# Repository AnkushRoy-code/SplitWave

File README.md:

<p align="center">
  <br>
</p>

# SplitWave
My very own custom wireless ergonomic split keyboard.

Splitwave is a 44 key column-staggered split keyboard that uses Choc switches.
Is is powered by SuperMini nRF52840 micro-controller. It is created during the
[Highway](https://highway.hackclub.com/) event of [Hackclub](https://hackclub.com/). The whole process of making it is journaled [here](https://github.com/AnkushRoy-code/SplitWave/blob/main/JOURNAL.md).

One day my work keyboard stopped working and I always dreamed of having those
fancy split keyboards but I was never lucky to have one at that same period of
time. HackClub announced Highway event, and I hopped into it!! The timing
couldn't have been any more perfect!!!

## Layout
<p align="center">
  <br>
  <b>Keys Layout of SplitWave</b>
</p>

## PCBs
SplitWave has a reversible PCB(which means you can order one PCB in stack and
use that for both left and right).
The KiCAD PCB file is located [here](https://github.com/AnkushRoy-code/SplitWave/blob/main/ergogen/pcb/board.kicad_pcb).

<table>
  <tr>
    <td align="center">
      <br>
      <b>Front Of the PCB</b>
    </td>
    <td align="center">
      <br>
      <b>Back Of the PCB</b>
    </td>
    <td align="center">
      <br>
      <b>PCB in KiCAD</b>
    </td>
  </tr>
</table>

## Case
The STL files for SplitWave are present [here](https://github.com/AnkushRoy-code/SplitWave/tree/main/ergogen/output/cases).
The cases are also hosted in printables.com [here](https://www.printables.com/model/1317576-splitwave-split-keyboard-cases)

<table>
  <tr>
    <td align="center">
      <br>
      <b>Top Case</b>
    </td>
    <td align="center">
      <br>
      <b>Left & Right Cases Top View</b>
    </td>
  </tr>
  <tr>
    <td align="center">
      <br>
      <b>Left & Right Cases Bottom View</b>
    </td>
    <td align="center">
      <br>
      <b>All Of Them Together</b>
    </td>
  </tr>
</table>

## Firmware
The firmware used for SplitWave is [ZMK](https://zmk.dev) and the prebuilt firmware can be found in the actions page of [this](https://github.com/AnkushRoy-code/zmk-config-splitwave) repo that I made.

## Photos
<table>
  <tr>
    <td align="center">
      <br>
    </td>
    <td align="center">
      <br>
    </td>
  </tr>
</table>

## Credits
[Hackclub](https://hackclub.com/) for giving me such an opportunity to work on my dream keyboard.

https://christianselig.com for inspiring me make my keyboard.

All the great tutorials in Youtube by [Joe Scotto](https://www.youtube.com/@joe_scotto) [Ben Vallack](https://www.youtube.com/@BenVallack) and many many more!!

Special thanks to https://flatfootfox.com for such a comprehensive and nice
tutorial on ergogen and thanks to the creator of ergogen himself and the
mantainers, contributors for making and mantaining such an amazing tool. Also
thanks a lot to ergogen discord/community for all their help!

Also thanks to https://github.com/GEIGEIGEIST/TOTEM for their readme. I didn't
know what goes into a keyboard readme so this readme is a lot inspired by the
Totem readme.

Lastly I will like to again thank hackclub for giving me such awesome
highschool years. Had a heck lot of fun all these years and had a blast making
my last [ysws](https://ysws.hackclub.com/) project. If you are (or know someone) younger than 18 or a
highschooler who is tech enthusiast then checkout hackclub it is really cool!

## License
This repo has an MIT License that in short means you can do whatever you want
with it without facing any lawsuit.

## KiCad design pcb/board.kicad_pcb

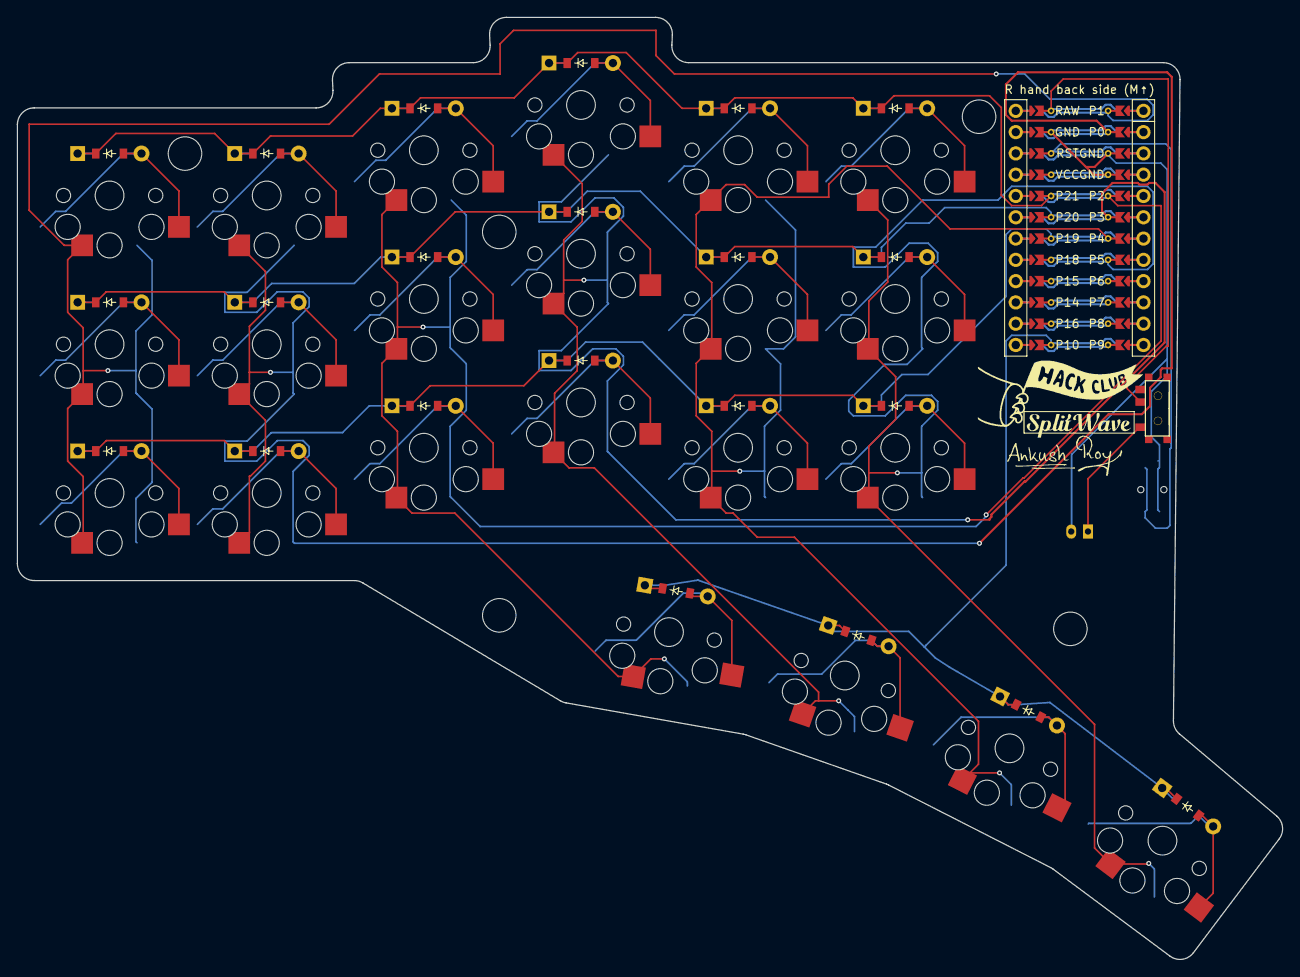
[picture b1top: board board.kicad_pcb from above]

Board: 2 copper layers, 151.0 x 112.4 mm, 48 parts (0 on the bottom side), 36 nets.

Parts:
B1: Panasonic_EVQPUL_EVQPUC
D1, D2, D3, D4, D5, D6, D7, D8, D9, D10, D11, D12, D13, D14, D15, D16, D17, D18, D19, D20, D21, D22: ComboDiode
JST1: JST_PH_S2B-PH-K_02x2.00mm_Angled
MCU1: mcu_supermini_nrf52840
S1, S2, S3, S4, S5, S6, S7, S8, S9, S10, S11, S12, S13, S14, S15, S16, S17, S18, S19, S20, S21, S22: PG1350
T1: SPDT_C128955

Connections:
GND: B1.1, JST1.2, MCU1.103, MCU1.104, MCU1.123
P0: MCU1.102, S4.1, S5.1, S6.1
P1: MCU1.101, S1.1, S2.1, S3.1
P2: MCU1.105, S7.1, S8.1, S9.1, S19.1
P3: MCU1.106, S10.1, S11.1, S12.1, S20.1
P4: MCU1.107, S13.1, S14.1, S15.1, S21.1
P5: MCU1.108, S16.1, S17.1, S18.1, S22.1
P10: D19.1, D20.1, D21.1, D22.1, MCU1.113
P19: D1.1, D4.1, D7.1, D10.1, D13.1, D16.1, MCU1.118
P20: D2.1, D5.1, D8.1, D11.1, D14.1, D17.1, MCU1.119
P21: D3.1, D6.1, D9.1, D12.1, D15.1, D18.1, MCU1.120
RAW: MCU1.124, T1.2
RST: B1.2, MCU1.122
four_cluster: D22.2, S22.2
index_bottom: D13.2, S13.2
index_home: D14.2, S14.2
index_top: D15.2, S15.2
inner_bottom: D16.2, S16.2
inner_home: D17.2, S17.2
inner_top: D18.2, S18.2
middle_bottom: D10.2, S10.2
middle_home: D11.2, S11.2
middle_top: D12.2, S12.2
one_cluster: D19.2, S19.2
outer_bottom: D1.2, S1.2
outer_home: D2.2, S2.2
outer_top: D3.2, S3.2
pinky_bottom: D4.2, S4.2
pinky_home: D5.2, S5.2
pinky_top: D6.2, S6.2
pos: JST1.1, T1.1
ring_bottom: D7.2, S7.2
ring_home: D8.2, S8.2
ring_top: D9.2, S9.2
three_cluster: D21.2, S21.2
two_cluster: D20.2, S20.2

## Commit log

2025-05-25 add: JOURNAL.md
2025-05-25 journal: 25/05/2025 - Did my research
2025-05-25 journal: 25/05/2025 + 2 hrs of planning and drawing
2025-05-25 Added Images
2025-05-25 Changed Image formatting so it shows in the gallery
    borrowed from: https://github.com/aargar1/argonaut/blob/main/JOURNAL.md
2025-05-27 journal: 26/05/2025 & 27/05/2025
2025-05-27 forgot to add the fillet property
2025-05-29 journal: 28/05/2025
2025-05-29 fix: journal.md added more info and formatting
2025-05-29 add: BOM.csv remove: StuffNeeded.md
2025-05-29 journal: 29/05/2025
2025-05-30 updated: BOM.csv
2025-05-30 journal: 30/05/2025
2025-05-30 add: journal: 30/05/2025
2025-05-31 journal: 31/05/2025 add: 3d files add: pcb complete: BOM
2025-05-31 Finished for the day 31st may 2025...
2025-06-01 journal: 1/06/2025
2025-06-02 add: zmk-config
2025-06-02 Some cleanup
2025-06-02 journal: 02/06/2025
2025-06-02 update: slikscreen of my pcb has some now drawings
2025-06-02 fix: submodules
2025-06-02 add: journal on readme addition
2025-06-03 changed the file structure a little
2025-06-03 changed the cases folder to the root folder
2025-06-03 update: zmk-config-splitwave update submodule
2025-06-03 updated: Readme
2025-06-03 fixed a pitfall in case design where i already fell. thank god i found it
2025-06-03 journal: 03/06/2025
2025-06-03 changed the cases a little again
2025-06-04 completed yesterday's journal
    also fixed the alt attrib in img tags
2025-06-04 my at my peak hapiness
2025-06-05 journal: 05/06/2025
2025-06-05 bought battery jack
2025-06-06 fixed my case design
2025-06-06 added top_case_compressed
2025-06-06 bumped zmk-config commit
2025-06-07 done
2025-06-08 There is nothing to worry about. I belive in myself. I have faced worse. I will find a solution. I always have. Everyone always does.
2025-06-10 added all of them together image
2025-06-10 journal: 10/06/2025
2025-06-10 coolest logo
2025-06-15 journal: 15/06/2025
2025-06-21 update: cases
2025-06-21 journal: 21/06/2025
2025-06-21 added images of updated cases
2025-06-21 bumb zmk commit
2025-06-23 removed useless cases
2025-06-23 update images again
    I mistakenly poofed my past work by force commiting from local :sob:
2025-06-27 journal: 27/06/2025
2025-06-30 journal: (27,28,29,30)/06/2025 I forgot to add all of them...
2025-06-30 added bought kit to bom
2025-07-04 journal 04/07/2025
2025-07-04 zmk version bumb
2025-07-06 journal 07/07/2025 what a day today was! read the journal for more info! + bumped zmk-config version!
2025-07-12 new commits to zmk
2025-07-12 update BOM
    fixed the 3d printing thing
2025-07-12 journal: 12/07/2025 - probably my biggest journal entry yet xd
2025-07-12 updated journal: 12/07/2025
2025-07-17 journal 16/07/2025
2025-07-19 journal 17&18/07/2025
2025-07-19 bumped submodle zmk-config-splitwave to latest commit
2025-07-19 journal 19/07/2025
2025-07-24 journal 24/07/2025
2025-07-27 journal 25/07/2025
2025-07-27 added last images
2025-08-11 backlog finished of journals since 25th july
2025-08-11 added images
    still need to add more images and format the currently added ones
2025-08-11 fixed the image formatting and also added 2 new images(?)
2025-08-11 fixed more images
